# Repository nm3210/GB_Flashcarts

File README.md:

# GB Flashcarts

## MBC5 Short
*Uploaded to OshPark: https://oshpark.com/shared_projects/A7b5nxHa*

&nbsp;
&nbsp;

This is my first try (plus updates) at routing the short version of an MBC5 flashcart, there certainly wasn't a lot of room!

Heavily inspired by [**HDR**](https://martinrefseth.com/)'s [updated MBC3](https://oshpark.com/shared_projects/YCtVNv4A) cart with clean borders and neat original/OEM features like the production date squares and (totally unnecessary) fiducial markings, as well as his own older [short MBC5 cart](https://oshpark.com/shared_projects/IOwfD0lC).

### Board features

\- GameBoy_GamePak_AGB-002 template from [github.com/**djedditt**/kicad-gamepaks](https://github.com/djedditt/kicad-gamepaks) (though I had to change all the rear shapes into netted pads)

\- Schematic mostly from [github.com/**HDR**/MBC5-Flashcart](https://github.com/HDR/MBC5-Flashcart)

\- Date markings and fiducials directly from [github.com/**HDR**/MBC3-Flashcart](https://github.com/HDR/MBC3-Flashcart) (though I tweaked the size a bit)

\- Some labels done via [github.com/gregdavill/KiBuzzard](https://github.com/gregdavill/KiBuzzard)

\- No traces connecting to the cart connector pins on the back side of the board, with a ground plane buffer - this seems to be a 'feature' on a lot of the OEM MBC3/MBC5 nintendo gameboy cartidges I've seen, though I don't know why. This restricted the routing on the board quite a bit!

### Bill of Materials
*Note*: need to order at a 0.8mm service (see OshPark's ["**2oz-0.8mm**"](https://docs.oshpark.com/services/two-layer-hhdc/)) for it to actually fit in a cart slot

| Reference | Part |
| :-- | :--: |
| U1 | TSOP-40/TSOP-48 MBM29F033C-90PTN, AM29F016B-90EC, or similar |
| U2 | MBC5 (from donor cart?) |
| U3 | 28-pin SOIC FM18W08 |
| C# | 100nF Capacitor 0603 |

### Changelog
\- **v1** around 2022-03-12

&emsp;First release, hoping for the best

\- **v2** around 2022-03-22

&emsp;Change from TSOP-40 to TSOP-48 to allow for more chip variants (including ones I bought of course)

&emsp;Fixed **wrong corner** marker on U1 (from lower-left to upper-right, specifically: the side with the **W**rite**E**nable pin should be facing south)

&emsp;Minor routing updates/cleanup

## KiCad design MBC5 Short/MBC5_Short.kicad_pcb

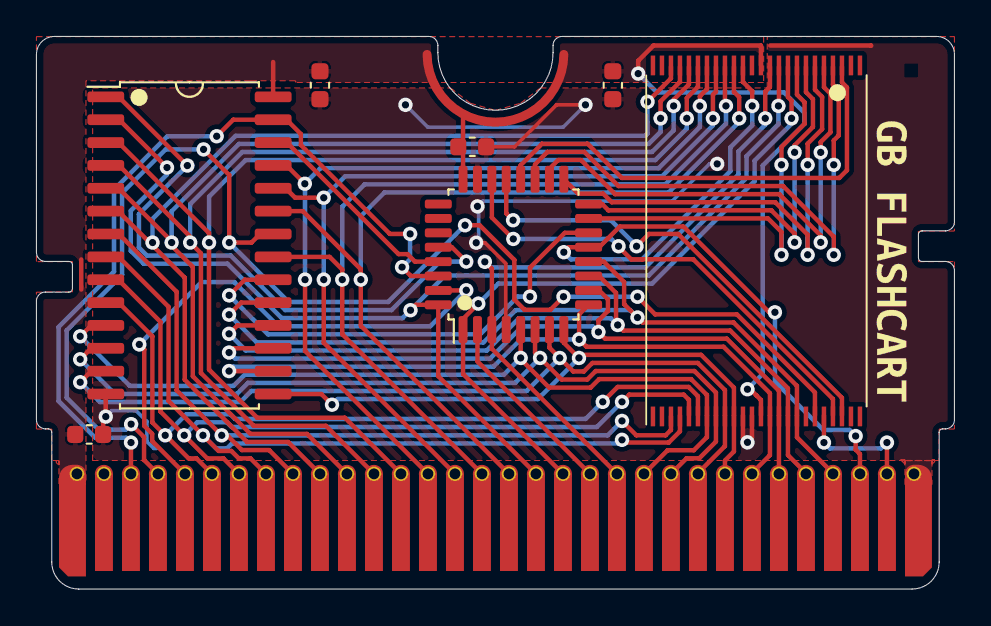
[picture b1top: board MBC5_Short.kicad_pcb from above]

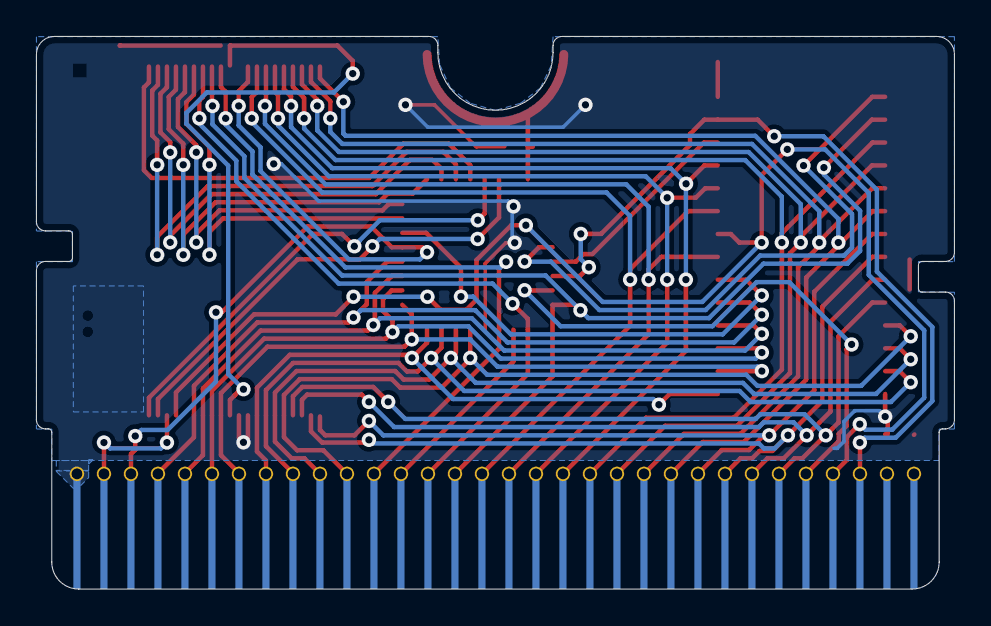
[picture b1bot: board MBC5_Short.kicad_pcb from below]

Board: 2 copper layers, 51.0 x 30.7 mm, 14 parts (3 on the bottom side), 42 nets.

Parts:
C1, C2, C3, C4: 100nF; C_0603_1608Metric
GNDPAD: Nintendo_2.25x2.25_Fiducial
J1: GameBoy_GamePak_AGB-002; GameBoy_GamePak_AGB-002_P1.50mm_Edge
PAD*: GB-ProductionIndicator
U1: 29F0; TSOP-I-48_18.4x12mm_P0.5mm
U2: MBC5; LQFP-32_7x7mm_P0.8mm
U3: FM18W08; SOIC-28W_7.5x17.9mm_P1.27mm
kibuzzard-622AB1EA: G***; kibuzzard-622AB1EA
kibuzzard-622AB126: G***; kibuzzard-622AB126
kibuzzard-622CFB3C: G***; kibuzzard-622CFB3C
kibuzzard-622CFB40: G***; kibuzzard-622CFB40

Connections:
+5V: C1.1, C2.1, C3.1, C4.1, J1.1, U1.11 (VCC~), U1.30 (VCC), U2.24 (PWR), U3.28 (VDD)
A0: J1.6, U1.4 (A0~), U3.10 (A0)
A1: J1.7, U1.3 (A1), U3.9 (A1)
A2: J1.8, U1.2 (A2), U3.8 (A2)
A3: J1.9, U1.1 (A3), U3.7 (A3)
A4: J1.10, U1.40 (A4), U3.6 (A4)
A5: J1.11, U1.39 (A5), U3.5 (A5)
A6: J1.12, U1.38 (A6), U3.4 (A6)
A7: J1.13, U1.37 (A7), U3.3 (A7)
A8: J1.14, U1.36 (A8), U3.25 (A8)
A9: J1.15, U1.35 (A9), U3.24 (A9)
A10: J1.16, U1.34 (A10), U3.21 (A10)
A11: J1.17, U1.33 (A11), U3.23 (A11)
A12: J1.18, U1.28 (A12), U2.32 (A12), U3.2 (A12)
A13: J1.19, U1.27 (A13), U2.1 (A13)
A14: J1.20, U2.2 (A14)
A15: J1.21, U1.29 (CE), U2.3 (A15)
AA13: U2.29 (AA13), U3.26 (A13)
AA14: U2.28 (AA14), U3.1 (A14)
CS: J1.5, U2.31 (/CS)
D0: J1.22, U1.5 (D0), U2.5 (D0), U3.11 (DQ0)
D1: J1.23, U1.6 (D1), U2.6 (D1), U3.12 (DQ1)
D2: J1.24, U1.7 (D2), U2.7 (D2), U3.13 (DQ2)
D3: J1.25, U1.8 (D3), U2.8 (D3), U3.15 (DQ3)
D4: J1.26, U1.12 (D4), U2.9 (D4), U3.16 (DQ4)
D5: J1.27, U1.13 (D5), U2.10 (D5), U3.17 (DQ5)
D6: J1.28, U1.14 (D6), U2.11 (D6), U3.18 (DQ6)
D7: J1.29, U1.15 (D7), U2.12 (D7), U3.19 (DQ7)
GND: C1.2, C2.2, C3.2, C4.2, J1.32, U1.9 (GND), U1.10 (GND), U2.4 (GND), U2.23 (GND), U3.14 (VSS)
RA14: U1.26 (A14), U2.15 (RA14)
RA15: U1.25 (A15), U2.16 (RA15)
RA16: U1.24 (A16), U2.17 (RA16)
RA17: U1.23 (A17), U2.18 (RA17)
RA18: U1.22 (A18), U2.19 (RA18)
RA19: U1.21 (A19), U2.20 (RA19)
RA20: U1.20 (A20), U2.21 (RA20)
RA21: U1.19 (A21), U2.22 (RA21)
RAMCS: U2.14 (/RAMCS), U3.20 (~CE)
RD: J1.4, U1.17 (OE~), U3.22 (~OE)
RESET: J1.30, U1.32 (RESET), U2.13 (/RESET)
WE_SND: J1.31, U1.18 (WE)
WR: J1.3, U2.30 (/WR), U3.27 (~WE)

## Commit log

2022-02-27 Add initial MBC5 Short kicad files
    The main body has been created from the GameBoy_GamePak_AGB-002 template via https://github.com/djedditt/kicad-gamepaks.
2022-02-28 Update MBC5 schematic properties, add title, etc.
2022-02-28 Add MBC5 chips (ROM, FRAM, MBC5) to schematic, not wired yet
    A few of the symbols came from HDR's https://github.com/HDR/Game-Boy-KiCad-Library, thank you thank you!!
2022-02-28 Add little jumper wires off each connection for ease
2022-02-28 Add nets between all components
    This generally, again, follows the work from HDR via https://github.com/HDR/MBC5-Flashcart/blob/29cbd084a0546ef0b45e91f31f956e2d148b7e93/MBC5%20Flashcart%20Schematic.pdf but I did try to corroborate 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
2022-02-28 Add unused rumble net, for curiosity
    From http://www.devrs.com/gb/files/rumble.gif.
2022-02-28 Add decoupling capacitors
2022-03-13 Update board specifications/clearances for OshPark service
    Even though I did all the routing with the original settings....😬
2022-03-13 Route entire board, bam
    This was a lot of work, but I really didn't feel like doing micro-commits for all the changes here and there
2022-03-13 Fix 48-pin SOP reference on schemetic with 40-pin footprint package
    I changed from the MBM29F033C which I incorrectly had associated with a TSOP-40 and swapped it with the similar AM29F032 package so the pins were all correct.
2022-03-13 Update GameBoy_GamePak_AGB-002 template with pads instead of just shapes
    This also copies over all the nets I was using for the pins
2022-03-13 Remove unused old-style schematic
2022-03-13 Initialize PCB configuration (blank template)
2022-03-13 Add PCB stackup to match a generic '2oz-0.8mm' service
    ala OshPark
2022-03-13 Add all gerber files used for oshpark submission
    via https://oshpark.com/shared_projects/VMSFCe2c
2022-03-13 Add readme with description and images
2022-03-13 Change size of thumbnails so they fit two-per-row
2022-03-13 Fixing rouge capital letters
2022-03-23 Change TSOP-40 to TSOP-48 to accomodate more chip variations
2022-03-23 Update MBC5 Short to v2
    with updated oshpark link, images, and gerber files
